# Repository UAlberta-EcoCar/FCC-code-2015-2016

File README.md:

Code for Ualberta ecocar team hydrogen fuel fuel cell controller using an at32uc3c processor.

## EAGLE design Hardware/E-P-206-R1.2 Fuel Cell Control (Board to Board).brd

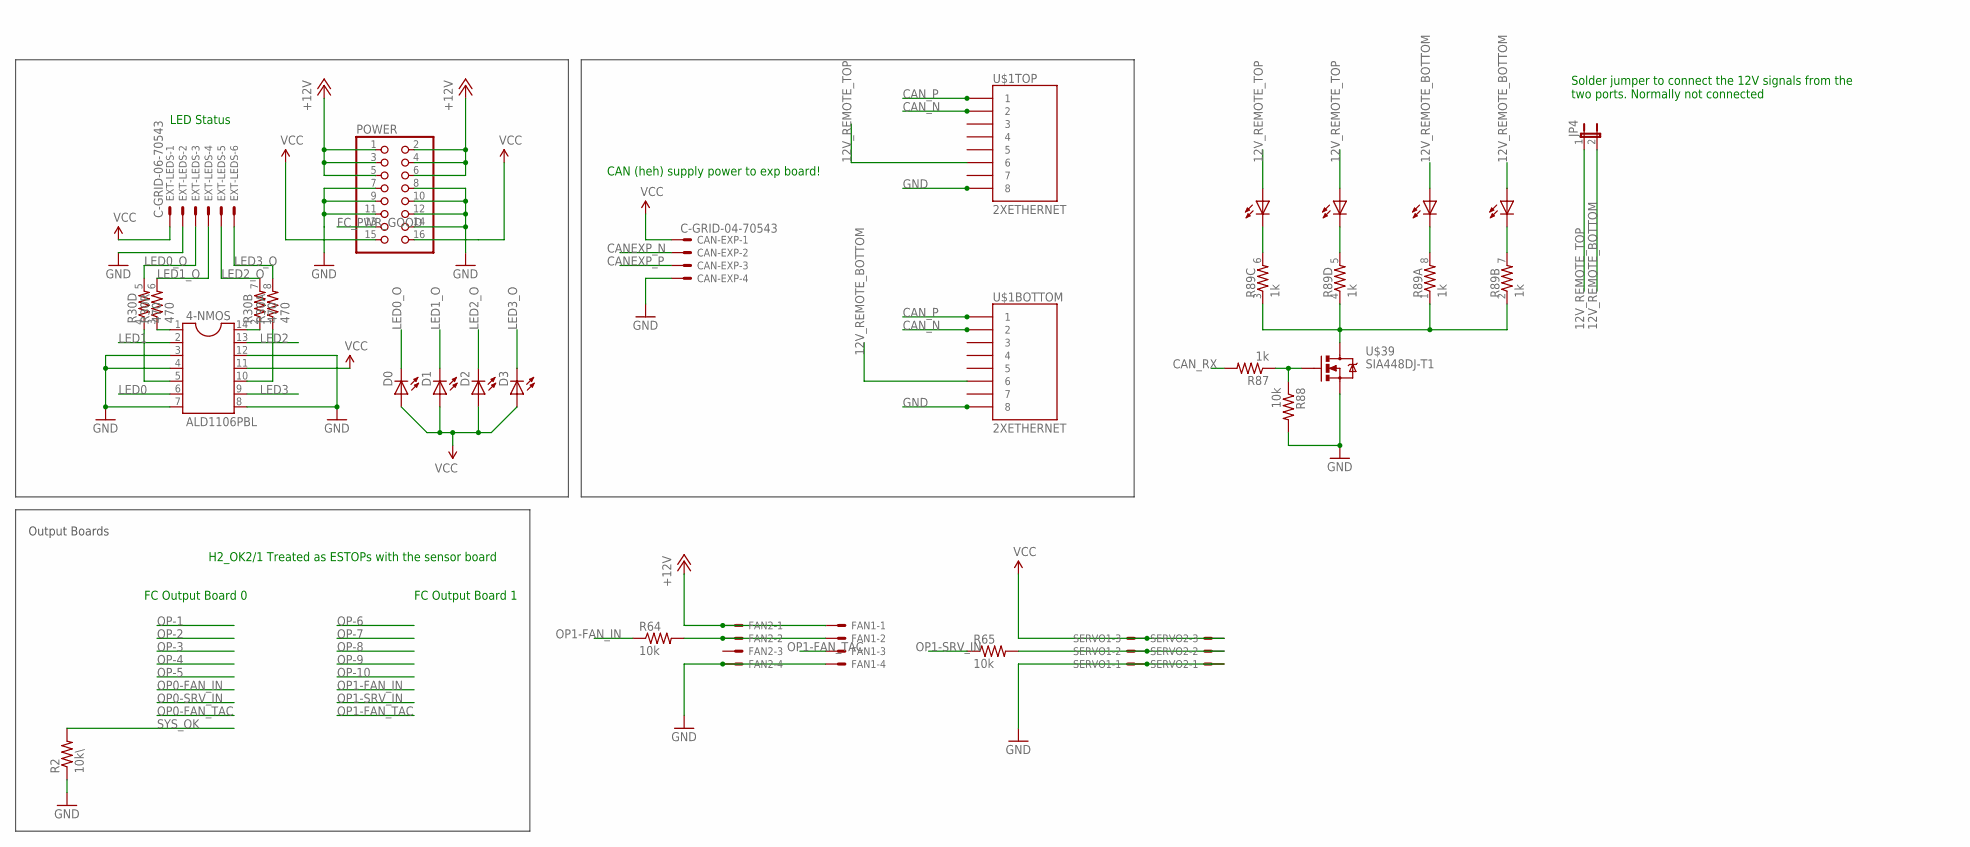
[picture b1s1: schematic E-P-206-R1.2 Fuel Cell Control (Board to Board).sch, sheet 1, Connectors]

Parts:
4-NMOS: ALD1106PBL; SOIC-14
CAN-EXP: C-GRID-04-70543; 70543-04
D0, D1, D2, D3: LED1206; LED-1206
EXT-LEDS: C-GRID-06-70543; 70543-06
FAN1, FAN2: C-GRID-04-70543; 70543-04
JP4: JUMPER-2SMD-NO; SJ_2S-NO
POWER: PINHD-2X8; 2X08
R2: 10k\; 0603-RES
R30: 470; 0603-ARV
R64, R65, R88: 10k; 0603-RES
R87: 1k; 0603-RES
R89: 1k; 0603-ARV
SERVO1, SERVO2: C-GRID-03-70543; 70543-03
U$1: 2XETHERNET
U$39: SIA448DJ-T1; SC70-6L

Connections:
12V_REMOTE_BOTTOM: JP4.2, U$1.B_6 (6), U$1.B_9 (A), U$1.B_11 (A)
12V_REMOTE_TOP: JP4.1, U$1.T_6 (6), U$1.T_9 (A), U$1.T_11 (A)
+12V: FAN1.1, FAN2.1, POWER.1, POWER.2, POWER.3, POWER.4, POWER.5, POWER.6; also elsewhere on the board
CANEXP_N: CAN-EXP.2; also elsewhere on the board
CANEXP_P: CAN-EXP.3; also elsewhere on the board
CAN_N: U$1.B_2 (2), U$1.T_2 (2); also elsewhere on the board
CAN_P: U$1.B_1 (1), U$1.T_1 (1); also elsewhere on the board
CAN_RX: R87.2; also elsewhere on the board
FC_PWR_GOOD: POWER.13; also elsewhere on the board
GND: 4-NMOS.3, 4-NMOS.4, 4-NMOS.7, 4-NMOS.8, 4-NMOS.12, CAN-EXP.4, EXT-LEDS.2, FAN1.4, FAN2.4, POWER.7, POWER.8, POWER.9, POWER.10, POWER.11, POWER.12, POWER.14, R2.1, R88.2, SERVO1.1, SERVO2.1, U$1.B_8 (8), U$1.T_8 (8), U$39.S@0 (S), U$39.S@1 (S); also elsewhere on the board
LED0: 4-NMOS.6; also elsewhere on the board
LED0_O: D0.C, EXT-LEDS.3, R30.5 (2)
LED1: 4-NMOS.2; also elsewhere on the board
LED1_O: D1.C, EXT-LEDS.4, R30.6 (2)
LED2: 4-NMOS.13; also elsewhere on the board
LED2_O: D2.C, EXT-LEDS.5, R30.7 (2)
LED3: 4-NMOS.9; also elsewhere on the board
LED3_O: D3.C, EXT-LEDS.6, R30.8 (2)
unnamed: 4-NMOS.5, R30.4 (1)
unnamed: 4-NMOS.1, R30.3 (1)
unnamed: 4-NMOS.14, R30.2 (1)
unnamed: 4-NMOS.10, R30.1
unnamed: R89.7 (2), U$1.B_10 (C)
unnamed: R89.5 (2), U$1.T_12 (C)
unnamed: R87.1, R88.1, U$39.G
unnamed: R89.6 (2), U$1.T_10 (C)
unnamed: R89.8 (2), U$1.B_12 (C)
unnamed: FAN1.2, FAN2.2, R64.2
unnamed: R65.2, SERVO1.2, SERVO2.2
unnamed: R89.1, R89.2 (1), R89.3 (1), R89.4 (1), U$39.D
OP1-FAN_IN: R64.1; also elsewhere on the board
OP1-FAN_TAC: FAN1.3; also elsewhere on the board
OP1-SRV_IN: R65.1; also elsewhere on the board
SYS_OK: R2.2; also elsewhere on the board
VCC: 4-NMOS.11, CAN-EXP.1, D0.A, D1.A, D2.A, D3.A, EXT-LEDS.1, POWER.15, POWER.16, SERVO1.3, SERVO2.3; also elsewhere on the board

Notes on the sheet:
FC Output Board 0
Output Boards
FC Output Board 1
LED Status
H2_OK2/1 Treated as ESTOPs with the sensor board
CAN (heh) supply power to exp board!
Solder jumper to connect the 12V signals from the two ports. Normally not connected

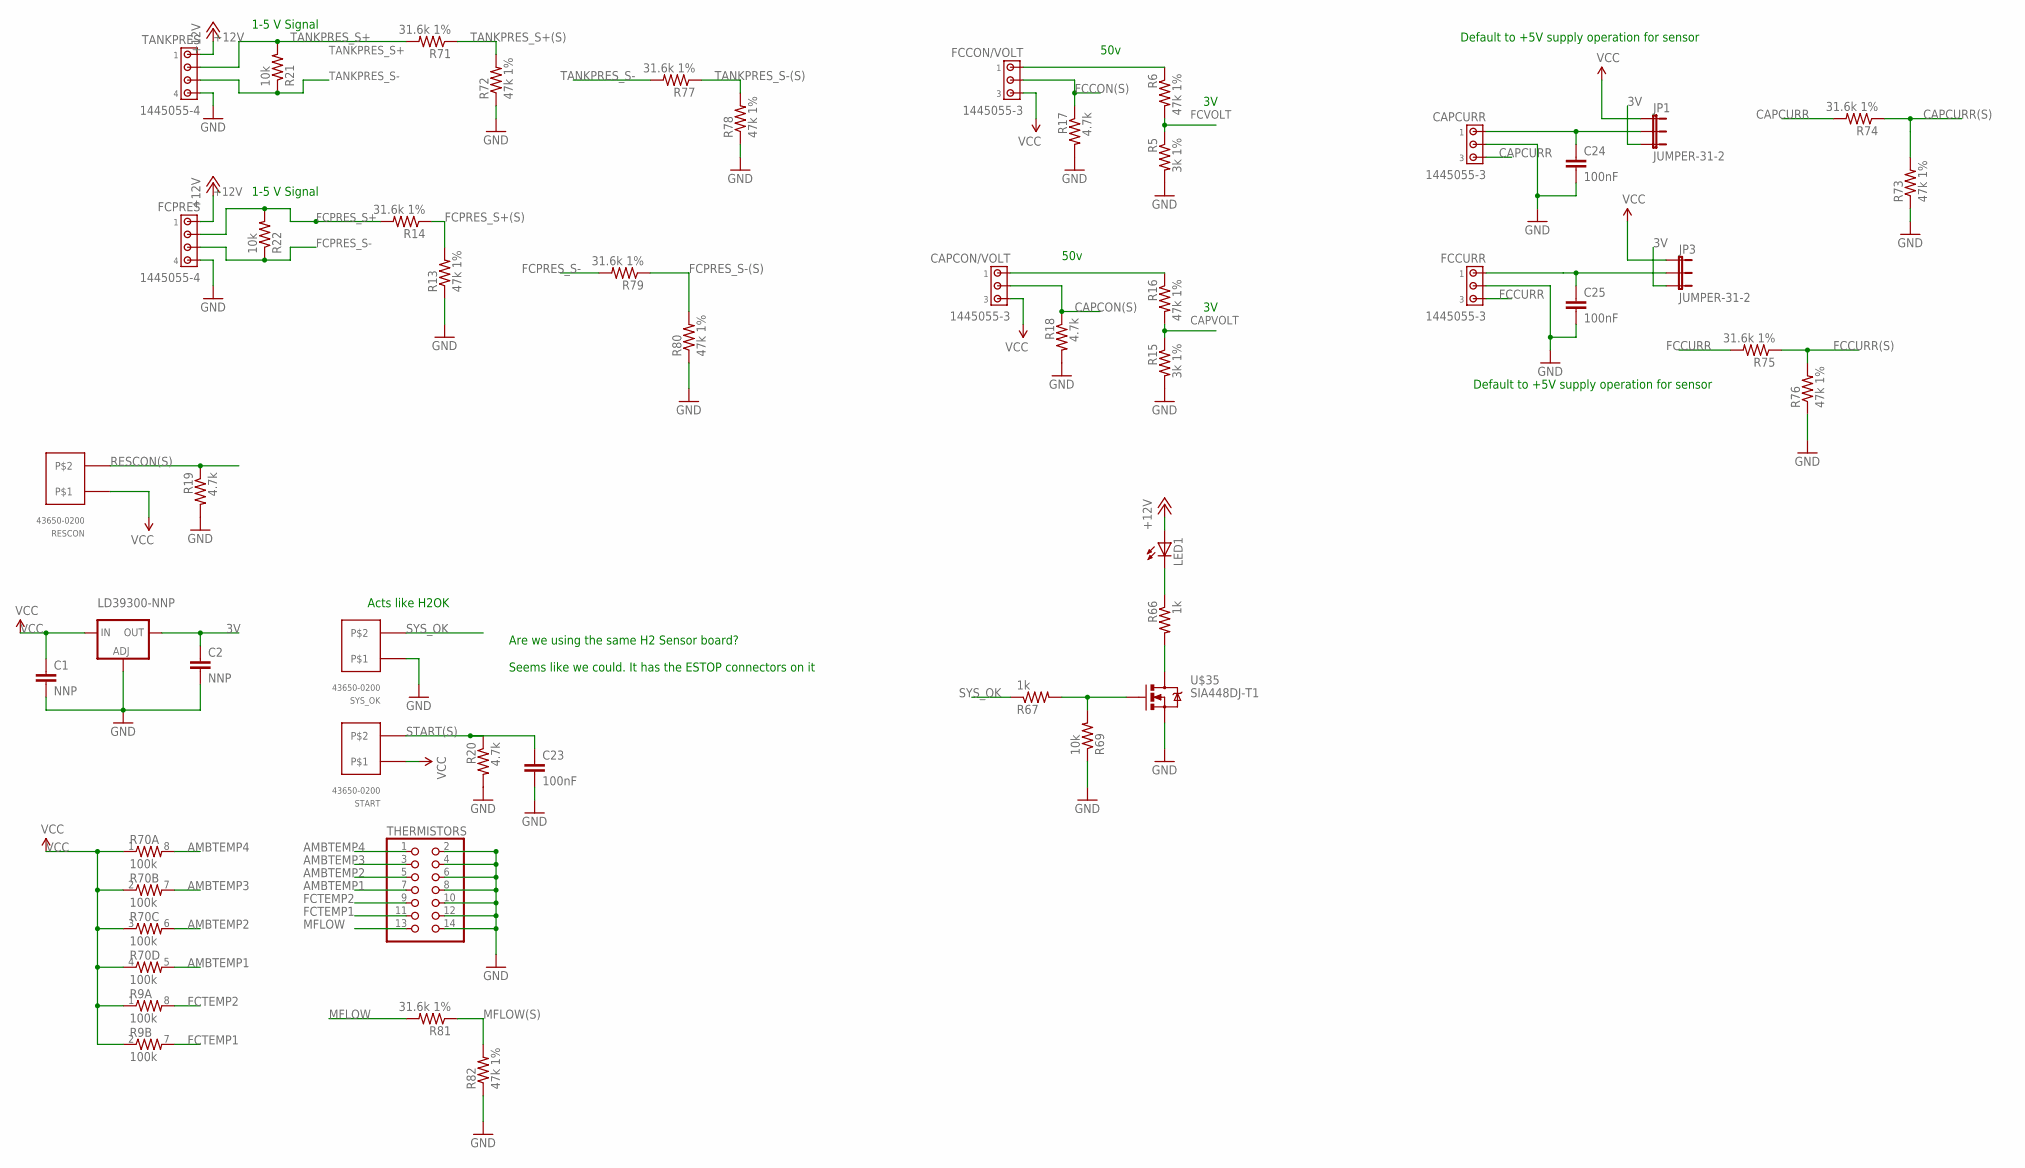
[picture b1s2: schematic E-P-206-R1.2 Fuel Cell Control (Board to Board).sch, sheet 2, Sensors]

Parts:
C1, C2: NNP; 1206
C23, C24, C25: 100nF; 0603-CAP
CAPCON/VOLT: 1445055-3
CAPCURR: 1445055-3
FCCON/VOLT: 1445055-3
FCCURR: 1445055-3
FCPRES: 1445055-4
JP1, JP3: JUMPER-31-2; SJ_3_PASTE1&2
LD39300-NNP: LD117ADT50TR; DPACK
LED1: LED1206; LED-1206
R5, R15: 3k 1%; 0603-RES
R6, R13, R16, R72, R73, R76, R78, R80, R82: 47k 1%; 0603-RES
R9, R70: 100k; 0603-ARV
R14, R71, R74, R75, R77, R79, R81: 31.6k 1%; 0603-RES
R17, R18, R19, R20: 4.7k; 0603-RES
R21, R22, R69: 10k; 0603-RES
R66, R67: 1k; 0603-RES
RESCON: 43650-0200
START: 43650-0200
SYS_OK: 43650-0200
TANKPRES: 1445055-4
THERMISTORS: PINHD-2X7; 2X07
U$35: SIA448DJ-T1; SC70-6L

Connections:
3V: C2.1, JP1.3, JP3.3, LD39300-NNP.4 (OUT)
+12V: FCPRES.1, LED1.A, TANKPRES.1; also elsewhere on the board
AMBTEMP1: R70.5 (2), THERMISTORS.7; also elsewhere on the board
AMBTEMP2: R70.6 (2), THERMISTORS.5; also elsewhere on the board
AMBTEMP3: R70.7 (2), THERMISTORS.3; also elsewhere on the board
AMBTEMP4: R70.8 (2), THERMISTORS.1; also elsewhere on the board
CAPCON(S): CAPCON/VOLT.2, R18.1; also elsewhere on the board
CAPCURR: CAPCURR.3, R74.2
CAPCURR(S): R73.2, R74.1; also elsewhere on the board
CAPVOLT: R15.1, R16.2; also elsewhere on the board
FCCON(S): FCCON/VOLT.2, R17.1; also elsewhere on the board
FCCURR: FCCURR.3, R75.2
FCCURR(S): R75.1, R76.2; also elsewhere on the board
FCPRES_S+: FCPRES.2, R14.2, R22.2
FCPRES_S+(S): R13.2, R14.1; also elsewhere on the board
FCPRES_S-: FCPRES.3, R22.1, R79.2
FCPRES_S-(S): R79.1, R80.2; also elsewhere on the board
FCTEMP1: R9.7 (2), THERMISTORS.11; also elsewhere on the board
FCTEMP2: R9.8 (2), THERMISTORS.9; also elsewhere on the board
FCVOLT: R5.1, R6.2; also elsewhere on the board
FCVOLT+: FCCON/VOLT.1, R6.1
FCVOLT+1: CAPCON/VOLT.1, R16.1
GND: C1.2, C2.2, C23.2, C24.2, C25.2, CAPCURR.2, FCCURR.2, FCPRES.4, LD39300-NNP.1 (ADJ), R5.2, R13.1, R15.2, R17.2, R18.2, R19.2, R20.2, R69.1, R72.1, R73.1, R76.1, R78.1, R80.1, R82.1, SYS_OK.P$2, TANKPRES.4, THERMISTORS.2, THERMISTORS.4, THERMISTORS.6, THERMISTORS.8, THERMISTORS.10, THERMISTORS.12, THERMISTORS.14, U$35.S@0 (S), U$35.S@1 (S); also elsewhere on the board
MFLOW: R81.2, THERMISTORS.13
MFLOW(S): R81.1, R82.2; also elsewhere on the board
unnamed: R66.2, U$35.D
unnamed: R67.2, R69.2, U$35.G
unnamed: LED1.C, R66.1
unnamed: C24.1, CAPCURR.1, JP1.2
unnamed: C25.1, FCCURR.1, JP3.2
RESCON(S): R19.1, RESCON.P$1; also elsewhere on the board
START(S): C23.1, R20.1, START.P$1; also elsewhere on the board
SYS_OK: R67.1, SYS_OK.P$1; also elsewhere on the board
TANKPRES_S+: R21.2, R71.2, TANKPRES.2
TANKPRES_S+(S): R71.1, R72.2; also elsewhere on the board
TANKPRES_S-: R21.1, R77.2, TANKPRES.3
TANKPRES_S-(S): R77.1, R78.2; also elsewhere on the board
VCC: C1.1, CAPCON/VOLT.3, FCCON/VOLT.3, JP1.1, JP3.1, LD39300-NNP.3 (IN), R9.1, R9.2 (1), R70.1, R70.2 (1), R70.3 (1), R70.4 (1), RESCON.P$2, START.P$2; also elsewhere on the board

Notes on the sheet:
Are we using the same H2 Sensor board? Seems like we could. It has the ESTOP connectors on it
Acts like H2OK
1-5 V Signal
50v
Default to +5V supply operation for sensor

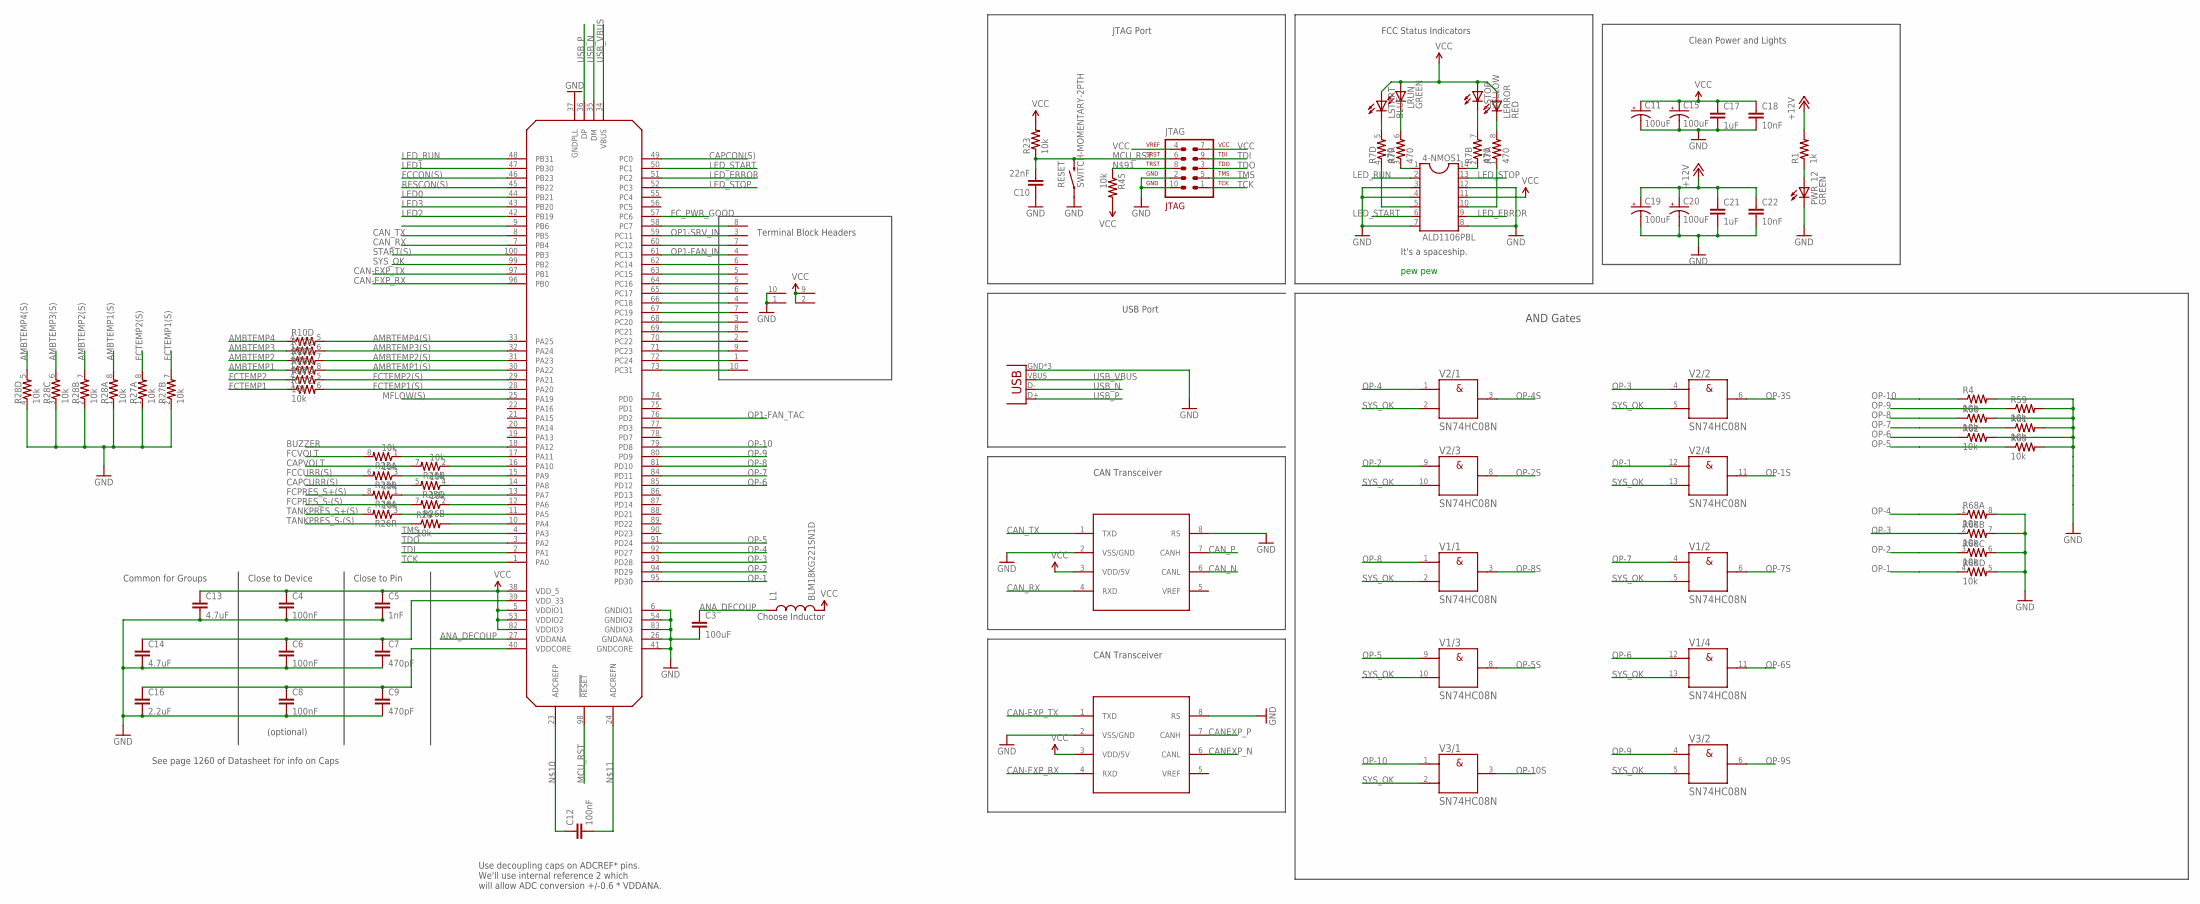
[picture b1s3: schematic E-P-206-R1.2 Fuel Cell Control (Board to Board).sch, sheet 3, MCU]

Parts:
4-NMOS1: ALD1106PBL; SOIC-14
C3: 100uF; 0805
C4, C6, C8: 100nF; 0603-CAP
C5: 1nF; 0603-CAP
C7, C9: 470pF; 0603-CAP
C10: 22nF; 0603-CAP
C11, C15, C19, C20: 100uF; PANASONIC_C
C12: 100nF; 0805
C13, C14: 4.7uF; 0805
C16: 2.2uF; 0805
C17, C21: 1uF; 0805
C18, C22: 10nF; 0603-CAP
JP2: USB; USB-MICROB
JTAG: 2x5; AVR-JTAG-10
L1: BLM18KG221SN1D; 0603
LERROR: RED; LED-1206
LRUN: GREEN; LED-1206
LSTART: BLUE; LED-1206
LSTOP: YELLOW; LED-1206
MCU: AT32UC3C1512; TQFP100
PWR_12: GREEN; LED-1206
R1: 1k; 0603-RES
R4, R23, R29, R45, R59, R60, R61, R62, R63: 10k; 0603-RES
R7: 470; 0603-ARV
R10, R25, R26, R27, R28, R68: 10k; 0603-ARV
RESET: SWITCH-MOMENTARY-2PTH; TACTILE-PTH
U$2, U$3: 10X1PCBBLOCK
U$4, U$36: MCP2551; 8-SOIC
V1, V2, V3: SN74HC08N; DIL14

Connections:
+12V: C19.+, C20.+, C21.1, C22.1, R1.2; also elsewhere on the board
AMBTEMP1: R10.1; also elsewhere on the board
AMBTEMP1(S): MCU.30 (PA22), R10.8 (2), R28.8 (2)
AMBTEMP2: R10.2 (1); also elsewhere on the board
AMBTEMP2(S): MCU.31 (PA23), R10.7 (2), R28.7 (2)
AMBTEMP3: R10.3 (1); also elsewhere on the board
AMBTEMP3(S): MCU.32 (PA24), R10.6 (2), R28.6 (2)
AMBTEMP4: R10.4 (1); also elsewhere on the board
AMBTEMP4(S): MCU.33 (PA25), R10.5 (2), R28.5 (2)
ANA_DECOUP: C3.1, L1.1, MCU.27 (VDDANA)
BUZZER: MCU.18 (PA12); also elsewhere on the board
CAN-EXP_RX: MCU.96 (PB0), U$36.4 (RXD)
CAN-EXP_TX: MCU.97 (PB1), U$36.1 (TXD)
CANEXP_N: U$36.6 (CANL); also elsewhere on the board
CANEXP_P: U$36.7 (CANH); also elsewhere on the board
CAN_N: U$4.6 (CANL); also elsewhere on the board
CAN_P: U$4.7 (CANH); also elsewhere on the board
CAN_RX: MCU.7 (PB4), U$4.4 (RXD); also elsewhere on the board
CAN_TX: MCU.8 (PB5), U$4.1 (TXD)
CAPCON(S): MCU.49 (PC0); also elsewhere on the board
CAPCURR(S): R25.5 (2); also elsewhere on the board
CAPVOLT: R25.7 (2); also elsewhere on the board
FCCON(S): MCU.46 (PB23); also elsewhere on the board
FCCURR(S): R25.6 (2); also elsewhere on the board
FCPRES_S+(S): R26.8 (2); also elsewhere on the board
FCPRES_S-(S): R26.7 (2); also elsewhere on the board
FCTEMP1: R27.3 (1); also elsewhere on the board
FCTEMP1(S): MCU.28 (PA20), R27.6 (2), R27.7 (2)
FCTEMP2: R27.4 (1); also elsewhere on the board
FCTEMP2(S): MCU.29 (PA21), R27.5 (2), R27.8 (2)
FCVOLT: R25.8 (2); also elsewhere on the board
FC_PWR_GOOD: MCU.57 (PC6); also elsewhere on the board
GND: 4-NMOS1.3, 4-NMOS1.4, 4-NMOS1.7, 4-NMOS1.8, 4-NMOS1.12, C3.2, C4.2, C5.2, C6.2, C7.2, C8.2, C9.2, C10.1, C11.-, C13.2, C14.2, C15.-, C16.2, C17.2, C18.2, C19.-, C20.-, C21.2, C22.2, JP2.GND, JP2.MT1 (GND), JP2.MT2 (GND), JTAG.2, JTAG.10, MCU.6 (GNDIO1), MCU.26 (GNDANA), MCU.37 (GNDPLL), MCU.41 (GNDCORE), MCU.54 (GNDIO2), MCU.83 (GNDIO3), PWR_12.C, R4.2, R27.1, R27.2 (1), R28.1, R28.2 (1), R28.3 (1), R28.4 (1), R59.2, R60.2, R61.2, R62.2, R63.2, R68.5 (2), R68.6 (2), R68.7 (2), R68.8 (2), RESET.1, U$2.10, U$3.1, U$4.2 (VSS/GND), U$4.8 (RS), U$36.2 (VSS/GND), U$36.8 (RS), V1.7 (-UB), V2.7 (-UB), V3.7 (-UB); also elsewhere on the board
LED0: MCU.44 (PB21); also elsewhere on the board
LED1: MCU.47 (PB30); also elsewhere on the board
LED2: MCU.42 (PB19); also elsewhere on the board
LED3: MCU.43 (PB20); also elsewhere on the board
LED_ERROR: 4-NMOS1.9, MCU.51 (PC2)
LED_RUN: 4-NMOS1.2, MCU.48 (PB31)
LED_START: 4-NMOS1.6, MCU.50 (PC1)
LED_STOP: 4-NMOS1.13, MCU.52 (PC3)
MCU_RST: C10.2, JTAG.6, MCU.98 (!RESET), R23.1, RESET.3 (2)
MFLOW(S): MCU.25 (PA19); also elsewhere on the board
unnamed: MCU.10 (PA4), R29.2
unnamed: MCU.12 (PA6), R26.2 (1)
unnamed: MCU.13 (PA7), R26.1
unnamed: C6.1, C7.1, C14.1, MCU.39 (VDD_33)
unnamed: C8.1, C9.1, C16.1, MCU.40 (VDDCORE)
unnamed: C12.1, MCU.23 (ADCREFP)
unnamed: C12.2, MCU.24 (ADCREFN)
unnamed: MCU.72 (PC24), U$2.1
unnamed: MCU.11 (PA5), R26.3 (1)
unnamed: MCU.70 (PC22), U$2.2
unnamed: MCU.68 (PC20), U$2.3
unnamed: MCU.14 (PA8), R25.4 (1)
unnamed: MCU.66 (PC18), U$2.4
unnamed: MCU.64 (PC16), U$2.5
unnamed: MCU.62 (PC14), U$2.6
unnamed: LSTART.C, R7.5 (2)
unnamed: LRUN.C, R7.6 (2)
unnamed: MCU.15 (PA9), R25.3 (1)
unnamed: MCU.16 (PA10), R25.2 (1)
unnamed: MCU.17 (PA11), R25.1
unnamed: MCU.60 (PC12), U$2.7
unnamed: MCU.58 (PC7), U$2.8
unnamed: 4-NMOS1.5, R7.4 (1)
unnamed: 4-NMOS1.1, R7.3 (1)
unnamed: PWR_12.A, R1.1
unnamed: MCU.63 (PC15), U$3.5
unnamed: MCU.65 (PC17), U$3.6
unnamed: MCU.67 (PC19), U$3.7
unnamed: MCU.69 (PC21), U$3.8
unnamed: MCU.71 (PC23), U$3.9
unnamed: MCU.73 (PC31), U$3.10
unnamed: 4-NMOS1.14, R7.2 (1)
unnamed: 4-NMOS1.10, R7.1
unnamed: LSTOP.C, R7.7 (2)
unnamed: LERROR.C, R7.8 (2)
unnamed: JTAG.8, R45.1
OP1-FAN_IN: MCU.61 (PC13), U$3.4; also elsewhere on the board
OP1-FAN_TAC: MCU.76 (PD2); also elsewhere on the board
OP1-SRV_IN: MCU.59 (PC11), U$3.3; also elsewhere on the board
OP-1: MCU.95 (PD30), R68.4 (1), V2.12 (A)
OP-1S: V2.11 (Y); also elsewhere on the board
OP-2: MCU.94 (PD29), R68.3 (1), V2.9 (A)
OP-2S: V2.8 (Y); also elsewhere on the board
OP-3: MCU.93 (PD28), R68.2 (1), V2.4 (A)
OP-3S: V2.6 (Y); also elsewhere on the board
OP-4: MCU.92 (PD27), R68.1, V2.1 (A)
OP-4S: V2.3 (Y); also elsewhere on the board
OP-5: MCU.91 (PD24), R63.1, V1.9 (A)
OP-5S: V1.8 (Y); also elsewhere on the board
OP-6: MCU.85 (PD12), R62.1, V1.12 (A)
OP-6S: V1.11 (Y); also elsewhere on the board
OP-7: MCU.84 (PD11), R61.1, V1.4 (A)
OP-7S: V1.6 (Y); also elsewhere on the board
OP-8: MCU.81 (PD10), R60.1, V1.1 (A)
OP-8S: V1.3 (Y); also elsewhere on the board
OP-9: MCU.80 (PD9), R59.1, V3.4 (A)
OP-9S: V3.6 (Y); also elsewhere on the board
OP-10: MCU.79 (PD8), R4.1, V3.1 (A)
OP-10S: V3.3 (Y); also elsewhere on the board
RESCON(S): MCU.45 (PB22); also elsewhere on the board
START(S): MCU.100 (PB3); also elsewhere on the board
SYS_OK: MCU.99 (PB2), V1.2 (B), V1.5 (B), V1.10 (B), V1.13 (B), V2.2 (B), V2.5 (B), V2.10 (B), V2.13 (B), V3.2 (B), V3.5 (B); also elsewhere on the board
TANKPRES_S+(S): R26.6 (2); also elsewhere on the board
TANKPRES_S-(S): R29.1; also elsewhere on the board
TCK: JTAG.1, MCU.1 (PA0)
TDI: JTAG.9, MCU.2 (PA1)
TDO: JTAG.3, MCU.3 (PA2)
TMS: JTAG.5, MCU.4 (PA3)
USB_N: JP2.D-, MCU.35 (DM)
USB_P: JP2.D+, MCU.36 (DP)
USB_VBUS: JP2.VBUS, MCU.34 (VBUS)
VCC: 4-NMOS1.11, C4.1, C5.1, C11.+, C13.1, C15.+, C17.1, C18.1, JTAG.4, JTAG.7, L1.2, LERROR.A, LRUN.A, LSTART.A, LSTOP.A, MCU.5 (VDDIO1), MCU.38 (VDD_5), MCU.53 (VDDIO2), MCU.82 (VDDIO3), R23.2, R45.2, U$2.9, U$3.2, U$4.3 (VDD/5V), U$36.3 (VDD/5V), V1.14 (+UB), V2.14 (+UB), V3.14 (+UB); also elsewhere on the board

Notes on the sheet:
Choose Inductor
Use decoupling caps on ADCREF* pins. We'll use internal reference 2 which will allow ADC conversion +/-0.6 * VDDANA.
Close to Pin
Close to Device
Common for Groups
JTAG Port
USB Port
(optional)
See page 1260 of Datasheet for info on Caps
CAN Transceiver
Terminal Block Headers
Clean Power and Lights
FCC Status Indicators
It's a spaceship.
pew pew
AND Gates

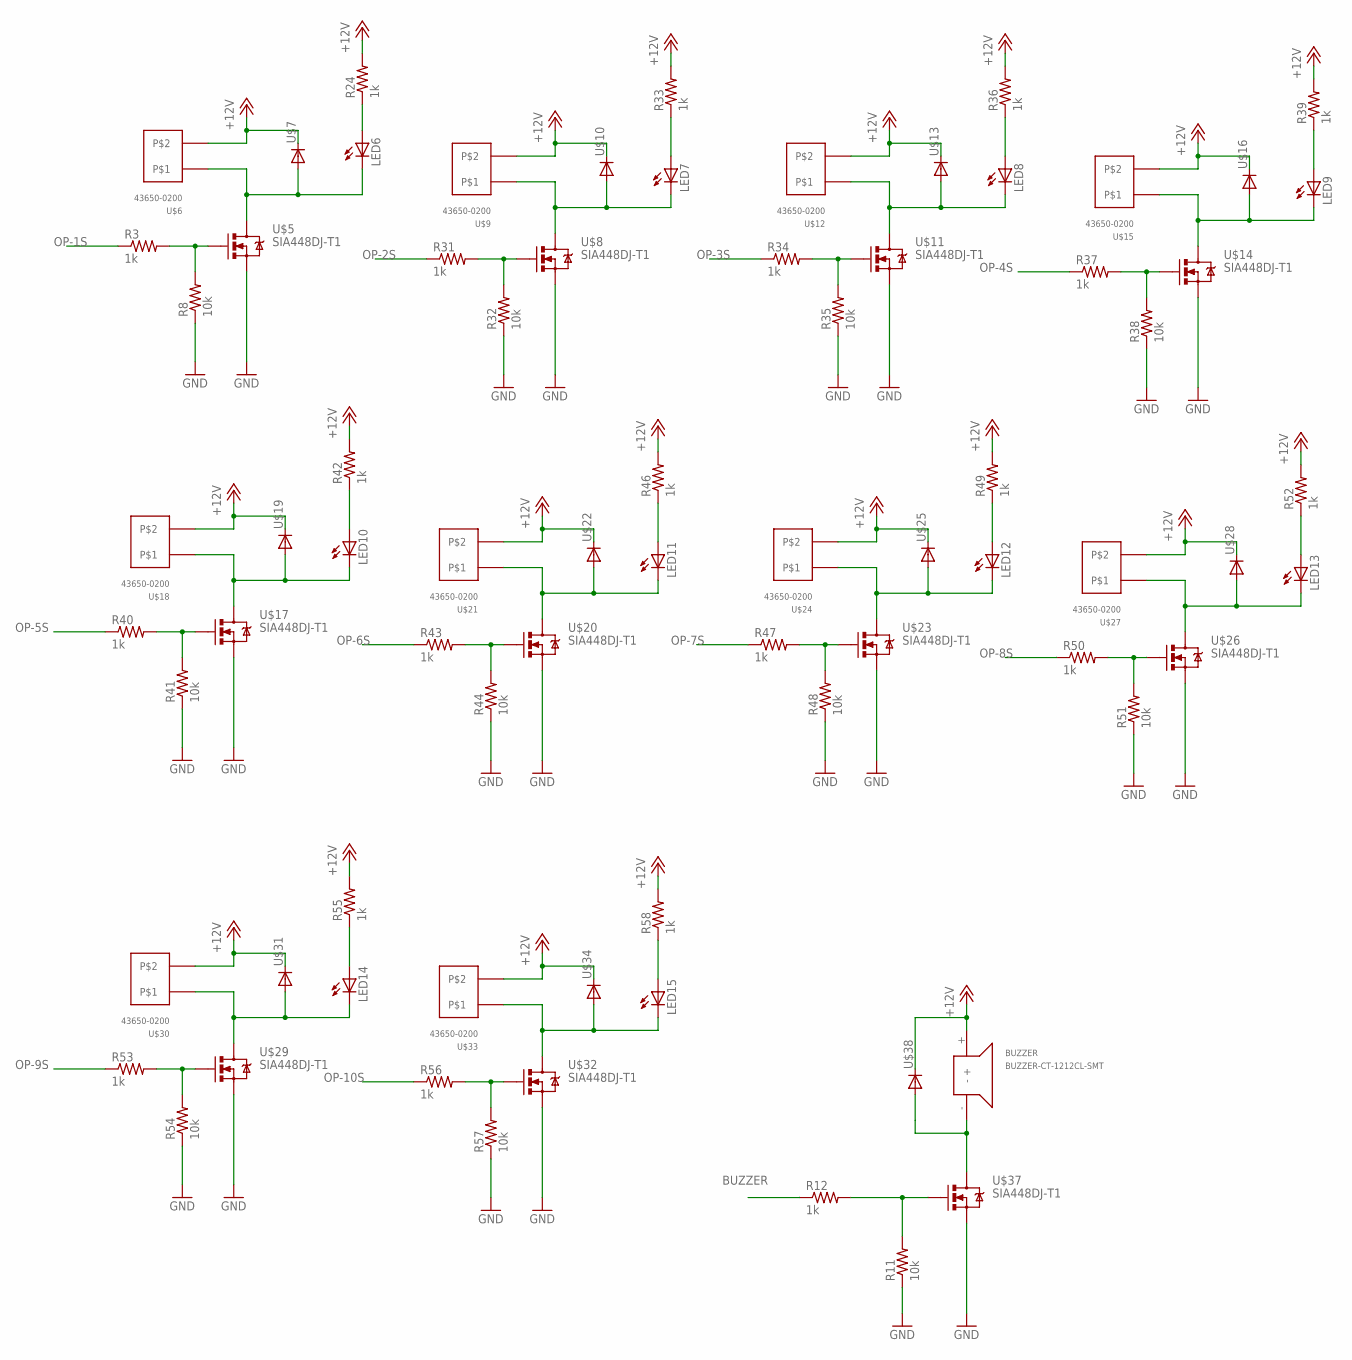
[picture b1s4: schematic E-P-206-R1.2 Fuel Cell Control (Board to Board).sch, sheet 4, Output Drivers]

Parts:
BUZZER: BUZZER-CT-1212CL-SMT; CT-1212CL-SMT
LED6, LED7, LED8, LED9, LED10, LED11, LED12, LED13, LED14, LED15: LED1206; LED-1206
R3, R12, R24, R31, R33, R34, R36, R37, R39, R40, R42, R43, R46, R47, R49, R50, R52, R53, R55, R56, R58: 1k; 0603-RES
R8, R11, R32, R35, R38, R41, R44, R48, R51, R54, R57: 10k; 0603-RES
U$5, U$8, U$11, U$14, U$17, U$20, U$23, U$26, U$29, U$32, U$37: SIA448DJ-T1; SC70-6L
U$6, U$9, U$12, U$15, U$18, U$21, U$24, U$27, U$30, U$33: 43650-0200
U$7, U$10, U$13, U$16, U$19, U$22, U$25, U$28, U$31, U$34, U$38: DIODE-DO214AC; DO214AC

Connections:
+12V: BUZZER.+, R24.2, R33.2, R36.2, R39.2, R42.2, R46.2, R49.2, R52.2, R55.2, R58.2, U$6.P$1, U$7.C, U$9.P$1, U$10.C, U$12.P$1, U$13.C, U$15.P$1, U$16.C, U$18.P$1, U$19.C, U$21.P$1, U$22.C, U$24.P$1, U$25.C, U$27.P$1, U$28.C, U$30.P$1, U$31.C, U$33.P$1, U$34.C, U$38.C; also elsewhere on the board
BUZZER: R12.1; also elsewhere on the board
GND: R8.1, R11.1, R32.1, R35.1, R38.1, R41.1, R44.1, R48.1, R51.1, R54.1, R57.1, U$5.S@0 (S), U$5.S@1 (S), U$8.S@0 (S), U$8.S@1 (S), U$11.S@0 (S), U$11.S@1 (S), U$14.S@0 (S), U$14.S@1 (S), U$17.S@0 (S), U$17.S@1 (S), U$20.S@0 (S), U$20.S@1 (S), U$23.S@0 (S), U$23.S@1 (S), U$26.S@0 (S), U$26.S@1 (S), U$29.S@0 (S), U$29.S@1 (S), U$32.S@0 (S), U$32.S@1 (S), U$37.S@0 (S), U$37.S@1 (S); also elsewhere on the board
unnamed: R3.2, R8.2, U$5.G
unnamed: R11.2, R12.2, U$37.G
unnamed: LED6.A, R24.1
unnamed: LED6.C, U$5.D, U$6.P$2, U$7.A
unnamed: R31.2, R32.2, U$8.G
unnamed: LED7.C, U$8.D, U$9.P$2, U$10.A
unnamed: LED7.A, R33.1
unnamed: R34.2, R35.2, U$11.G
unnamed: BUZZER.-, U$37.D, U$38.A
unnamed: LED8.C, U$11.D, U$12.P$2, U$13.A
unnamed: LED8.A, R36.1
unnamed: R37.2, R38.2, U$14.G
unnamed: LED9.C, U$14.D, U$15.P$2, U$16.A
unnamed: LED9.A, R39.1
unnamed: R40.2, R41.2, U$17.G
unnamed: LED10.C, U$17.D, U$18.P$2, U$19.A
unnamed: LED13.A, R52.1
unnamed: R43.2, R44.2, U$20.G
unnamed: LED11.C, U$20.D, U$21.P$2, U$22.A
unnamed: LED12.A, R49.1
unnamed: R47.2, R48.2, U$23.G
unnamed: LED12.C, U$23.D, U$24.P$2, U$25.A
unnamed: LED11.A, R46.1
unnamed: R50.2, R51.2, U$26.G
unnamed: LED13.C, U$26.D, U$27.P$2, U$28.A
unnamed: LED10.A, R42.1
unnamed: R53.2, R54.2, U$29.G
unnamed: LED14.C, U$29.D, U$30.P$2, U$31.A
unnamed: LED14.A, R55.1
unnamed: R56.2, R57.2, U$32.G
unnamed: LED15.C, U$32.D, U$33.P$2, U$34.A
unnamed: LED15.A, R58.1
OP-1S: R3.1; also elsewhere on the board
OP-2S: R31.1; also elsewhere on the board
OP-3S: R34.1; also elsewhere on the board
OP-4S: R37.1; also elsewhere on the board
OP-5S: R40.1; also elsewhere on the board
OP-6S: R43.1; also elsewhere on the board
OP-7S: R47.1; also elsewhere on the board
OP-8S: R50.1; also elsewhere on the board
OP-9S: R53.1; also elsewhere on the board
OP-10S: R56.1; also elsewhere on the board

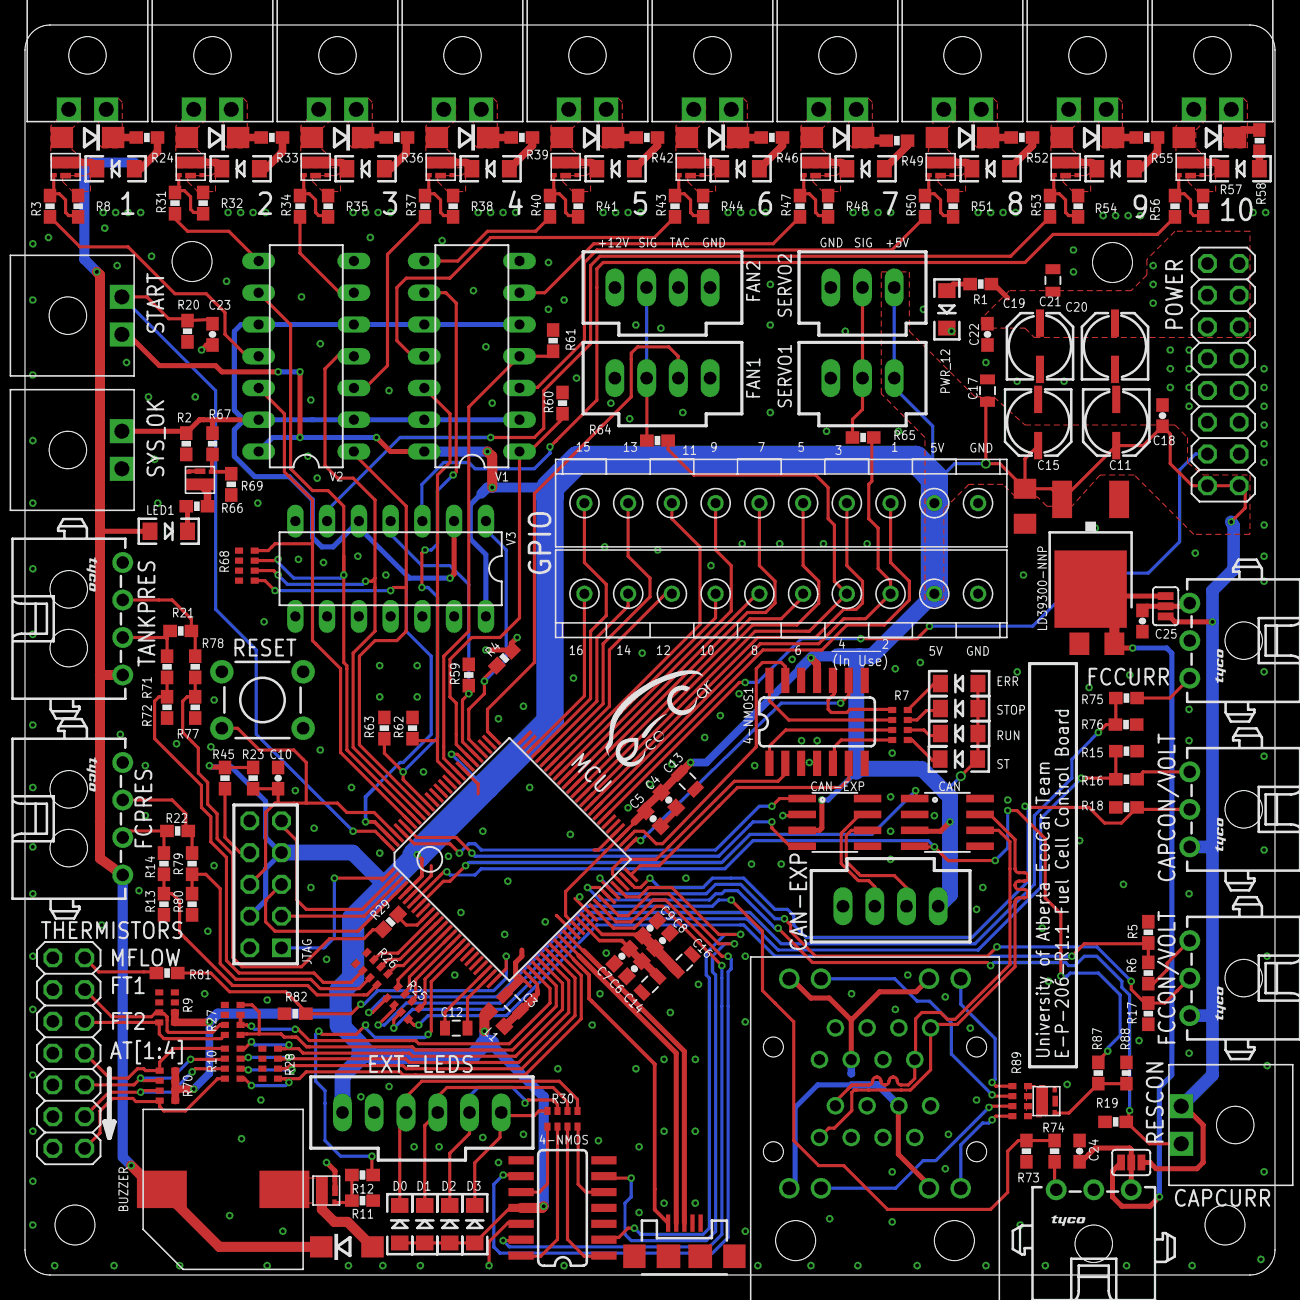
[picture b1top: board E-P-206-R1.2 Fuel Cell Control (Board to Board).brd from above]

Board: 2 copper layers, 100.0 x 100.0 mm, 201 parts (1 on the bottom side), 180 nets.

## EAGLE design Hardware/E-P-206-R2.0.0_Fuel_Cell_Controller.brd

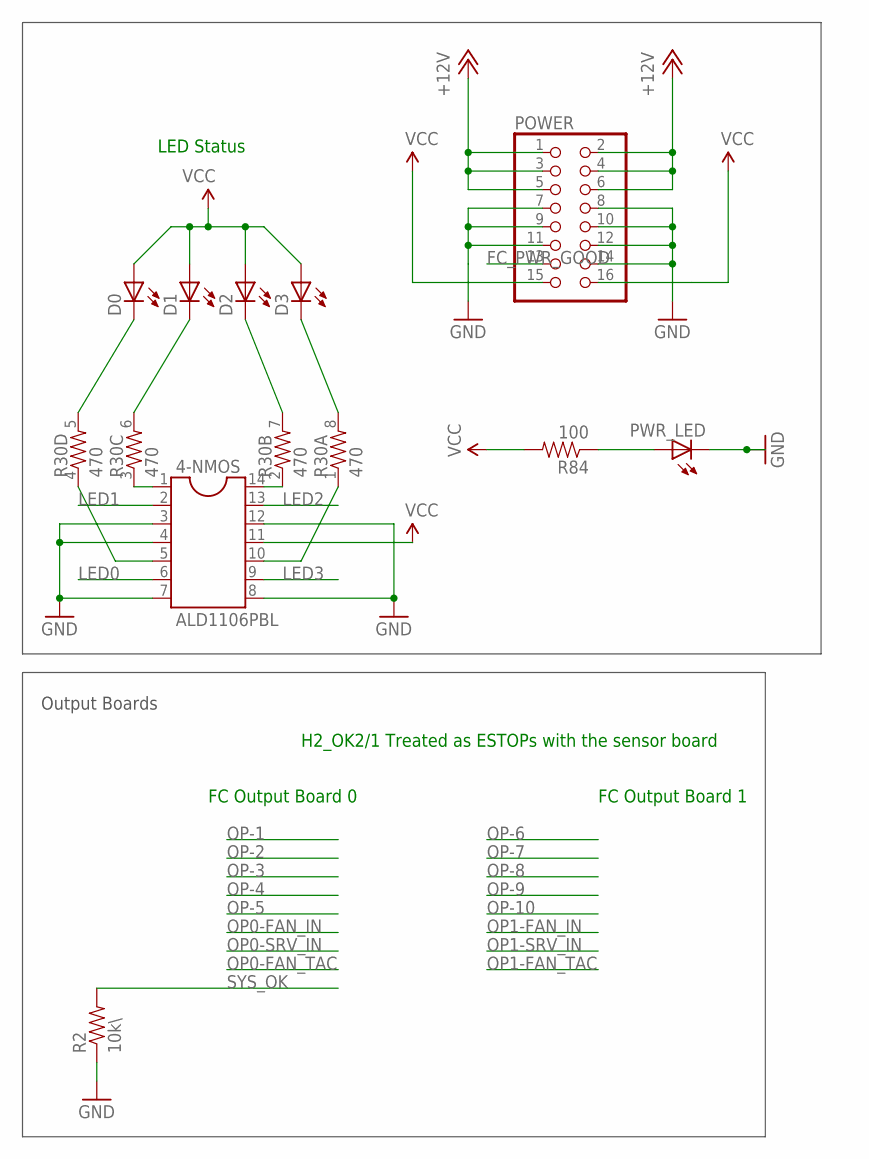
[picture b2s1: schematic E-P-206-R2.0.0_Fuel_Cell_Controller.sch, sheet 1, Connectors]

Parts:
4-NMOS: ALD1106PBL; SOIC-14
D0, D1, D2, D3: LED1206; LED-1206
POWER: PINHD-2X8; 2X08
PWR_LED: LED1206; LED-1206
R2: 10k\; 0603-RES
R30: 470; 0603-ARV
R84: 100; 0603-RES

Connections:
+12V: POWER.1, POWER.2, POWER.3, POWER.4, POWER.5, POWER.6; also elsewhere on the board
FC_PWR_GOOD: POWER.13
GND: 4-NMOS.3, 4-NMOS.4, 4-NMOS.7, 4-NMOS.8, 4-NMOS.12, POWER.7, POWER.8, POWER.9, POWER.10, POWER.11, POWER.12, POWER.14, PWR_LED.C, R2.1; also elsewhere on the board
LED0: 4-NMOS.6; also elsewhere on the board
LED0_O: D0.C, R30.5 (2)
LED1: 4-NMOS.2; also elsewhere on the board
LED1_O: D1.C, R30.6 (2)
LED2: 4-NMOS.13; also elsewhere on the board
LED2_O: D2.C, R30.7 (2)
LED3: 4-NMOS.9; also elsewhere on the board
LED3_O: D3.C, R30.8 (2)
unnamed: 4-NMOS.5, R30.4 (1)
unnamed: 4-NMOS.1, R30.3 (1)
unnamed: 4-NMOS.14, R30.2 (1)
unnamed: 4-NMOS.10, R30.1
unnamed: PWR_LED.A, R84.1
SYS_OK: R2.2; also elsewhere on the board
VCC: 4-NMOS.11, D0.A, D1.A, D2.A, D3.A, POWER.15, POWER.16, R84.2; also elsewhere on the board

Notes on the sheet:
FC Output Board 0
Output Boards
FC Output Board 1
LED Status
H2_OK2/1 Treated as ESTOPs with the sensor board

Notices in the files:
parts and their libraries:
SparkFun: Licensing: CC v3.0 Share-Alike You are welcome to use this library for commercial purposes.
SparkFun-Capacitors: Licensing: Creative Commons ShareAlike 4.0 International - https://creativecommons.org/licenses/by-sa/4.0
